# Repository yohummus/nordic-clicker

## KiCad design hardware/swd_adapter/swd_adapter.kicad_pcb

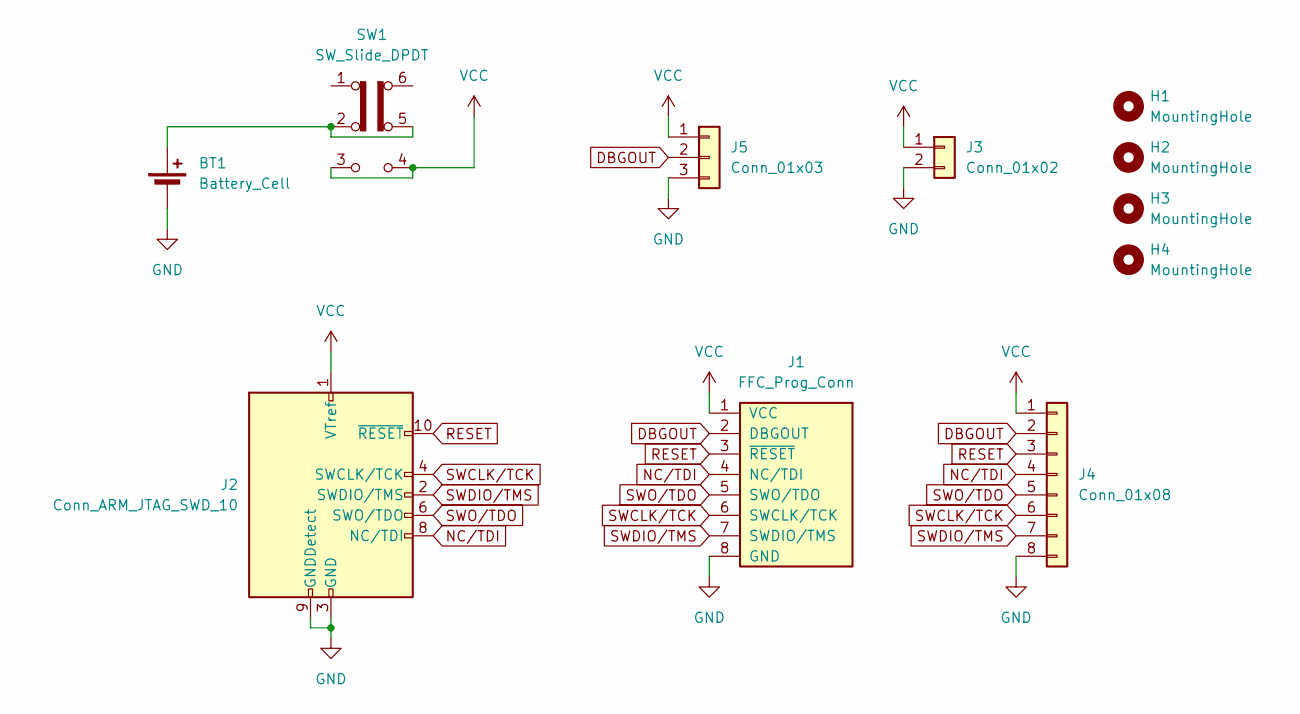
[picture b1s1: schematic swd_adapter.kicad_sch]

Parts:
BT1: Battery_Cell; BatteryHolder_Keystone_1060_1x2032; MPN 1060TR; Mouser-PN 534-1060TR
H1, H2, H3, H4: MountingHole; MountingHole_3.2mm_M3
J1: FFC_Prog_Conn; Molex_505110-0892; MPN 505110-0892; Mouser-PN 538-505110-0892
J2: Conn_ARM_JTAG_SWD_10; PinHeader_2x05_P1.27mm_Vertical_SMD; MPN 4048; Mouser-PN 485-4048
J3: Conn_01x02; PinHeader_1x02_P2.54mm_Vertical
J4: Conn_01x08; PinHeader_1x08_P2.54mm_Vertical
J5: Conn_01x03; PinHeader_1x03_P2.54mm_Vertical
SW1: SW_Slide_DPDT; SW_CK_JS202011CQN_DPDT_Straight; MPN JS202011CQN; Mouser-PN 611-JS202011CQN

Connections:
DBGOUT: J1.2 (DBGOUT), J4.2, J5.2
GND: BT1.2 (-), J1.8 (GND), J2.3 (GND), J2.5 (GND), J2.9 (GNDDetect), J3.2, J4.8, J5.3
NC/TDI: J1.4 (NC/TDI), J2.8 (NC/TDI), J4.4
unnamed: BT1.1 (+), SW1.2 (B), SW1.5 (B)
RESET: J1.3 (~RESET), J2.10 (~RESET), J4.3
SWCLK/TCK: J1.6 (SWCLK/TCK), J2.4 (SWCLK/TCK), J4.6
SWDIO/TMS: J1.7 (SWDIO/TMS), J2.2 (SWDIO/TMS), J4.7
SWO/TDO: J1.5 (SWO/TDO), J2.6 (SWO/TDO), J4.5
VCC: J1.1 (VCC), J2.1 (VTref), J3.1, J4.1, J5.1, SW1.3 (C), SW1.4 (A)

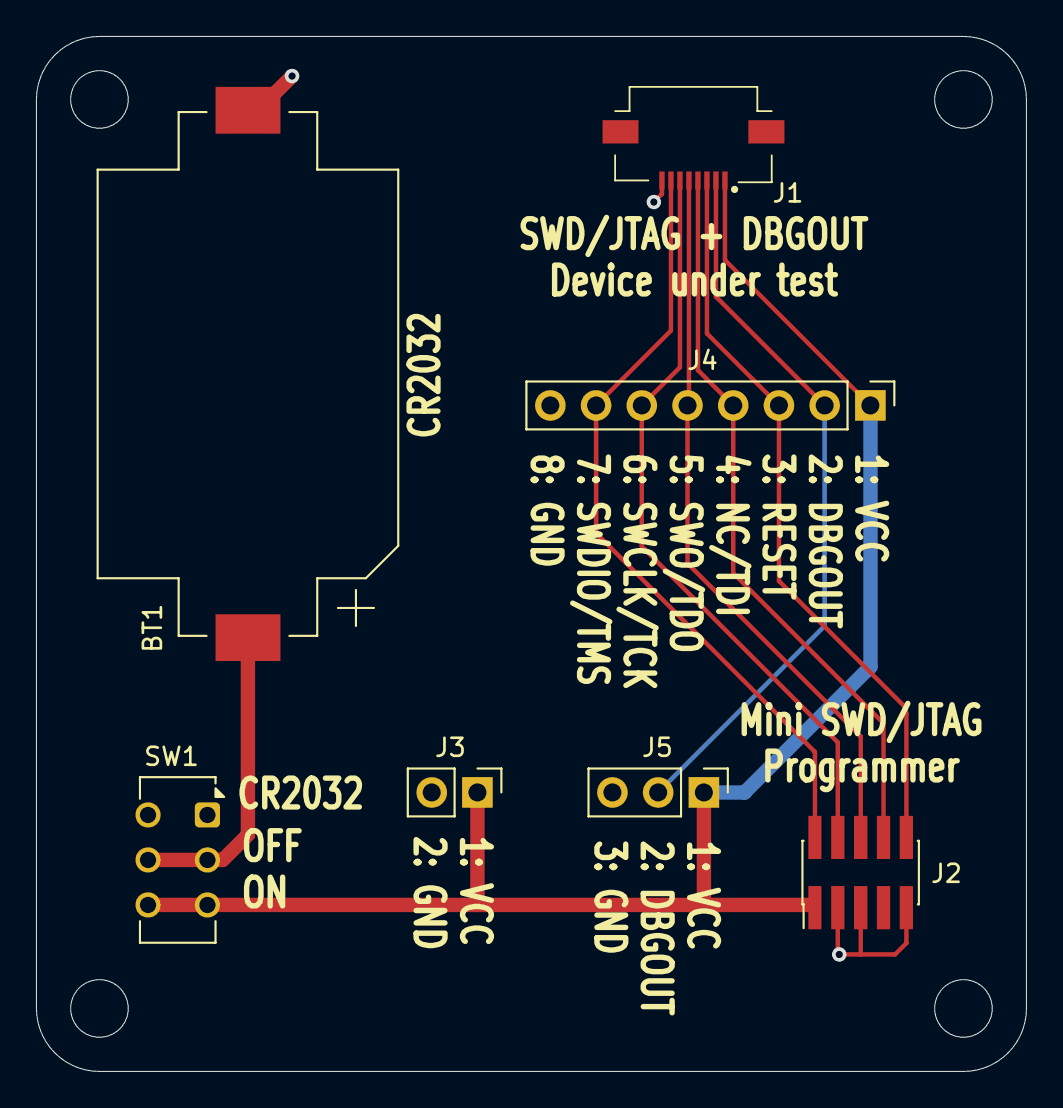
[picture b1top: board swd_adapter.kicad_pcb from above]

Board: 2 copper layers, 55.0 x 57.5 mm, 11 parts (0 on the bottom side), 9 nets.

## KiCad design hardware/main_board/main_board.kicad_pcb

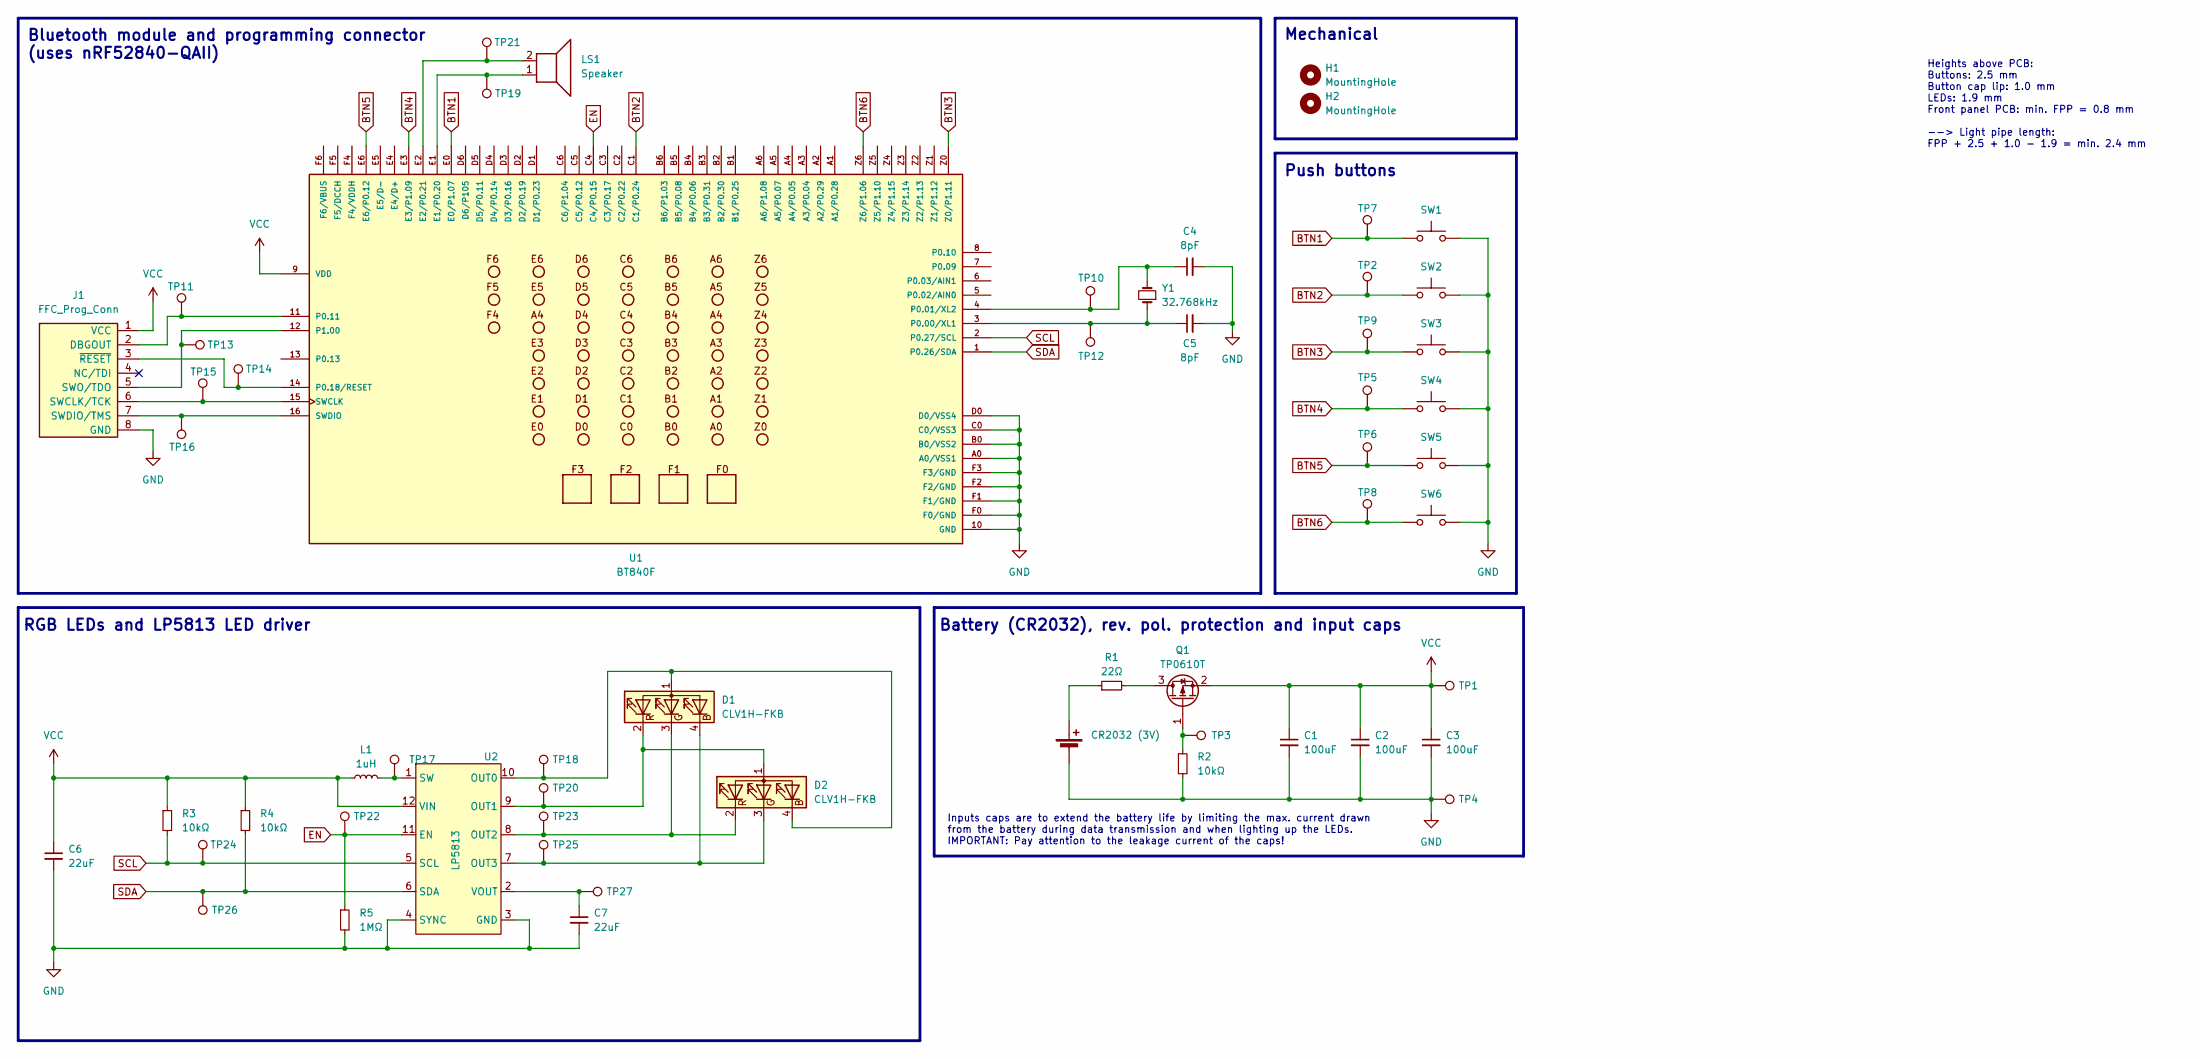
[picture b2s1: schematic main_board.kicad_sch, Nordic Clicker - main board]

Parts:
BT1: Keystone_2991; MPN 2991; Mouser-PN 534-2991
BT2: CR2032 (3V); BAT-HLD-001; MPN BAT-HLD-001; Mouser-PN 712-BAT-HLD-001
C1, C2, C3: 100uF; C_1206_3216Metric; Voltage 10V; Tolerance 20%; MPN C3216X5R1A107M160AC; Mouser-PN 810-C3216X5R1A107M
C4, C5: 8pF; C_0603_1608Metric; Voltage 25V; Tolerance 0.5pF; MPN 06033A8R0DAT2A; Mouser-PN 581-06033A8R0DAT2A
C6, C7: 22uF; C_0603_1608Metric; Voltage 16V; Tolerance 20%; MPN GRM188C61C226ME01J; Mouser-PN 81-GRM188C61C226ME1J
D1, D2: CLV1H-FKB; PLCC4_CLV1H-FKB; MPN CLV1H-FKB-CMPRTHKBB2367453; Mouser-PN 941-CLV1HBCTKB237453
H1, H2: MountingHole; Hole_2.5mm_Keepout_4mm
J1: FFC_Prog_Conn; Molex_505110-0892; MPN 505110-0892; Mouser-PN 538-505110-0892
L1: 1uH; SRP4020TA; MPN SRP4020TA-1R0M; Mouser-PN 652-SRP4020TA-1R0M
LS1: Speaker; Buzzer_Mallory_AST1109MLTRQ; MPN AST1109MLTRQ; Mouser-PN 539-AST1109MLTRQ
Q1: TP0610T; SOT-23; MPN SI2323DDS-T1-GE3; Mouser-PN 78-SI2323DDS-T1-GE3
R1: 22Ω; R_0603_1608Metric; Voltage 75V; Tolerance 1%; MPN CRCW060322R0FKEAC; Mouser-PN 71-CRCW060322R0FKEAC
R2, R3, R4: 10kΩ; R_0603_1608Metric; Voltage 75V; Tolerance 1%; MPN CRCW060310K0FKEAC; Mouser-PN 71-CRCW060310K0FKEAC
R5: 1MΩ; R_0603_1608Metric; Voltage 75V; Tolerance 1%; MPN CRCW06031M00FKEAC; Mouser-PN 71-CRCW06031M00FKEAC
SW1, SW2, SW3, SW4, SW5, SW6: PTS810SJG250SMTR LFS; PTS810; MPN PTS810SJG250SMTR LFS; Mouser-PN 611-PTS810SJG250SMTR
TP1, TP2, TP3, TP4, TP5, TP6, TP7, TP8, TP9, TP10, TP11, TP12, TP13, TP14, TP15, TP16, TP17, TP18, TP19, TP20, TP21, TP22, TP23, TP24, TP25, TP26, TP27: Test_Point; TestPoint_Pad_D1.0mm
U1: BT840F; MPN BT840F; Mouser-PN 308-BT840F
U2: LP5813; WSON-12; MPN LP5813CDRRR; Mouser-PN 595-LP5813CDRRR
Y1: 32.768kHz; ABS07AIG; MPN ABS07-32.768KHZ-9-T; Mouser-PN 815-ABS07-32.768K9T

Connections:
BTN1: SW1.2, TP7.1, U1.E0 (E0/P1.07)
BTN2: SW2.2, TP2.1, U1.C1 (C1/P0.24)
BTN3: SW3.2, TP9.1, U1.Z0 (Z0/P1.11)
BTN4: SW4.2, TP5.1, U1.E3 (E3/P1.09)
BTN5: SW5.2, TP6.1, U1.E6 (E6/P0.12)
BTN6: SW6.2, TP8.1, U1.Z6 (Z6/P1.06)
EN: R5.1, TP22.1, U1.C4 (C4/P0.15), U2.11 (EN)
GND: BT1.1 (-), C1.2, C2.2, C3.2, C4.2, C5.2, C6.2, C7.2, J1.8 (GND), R2.2, R5.2, SW1.1, SW2.1, SW3.1, SW4.1, SW5.1, SW6.1, TP4.1, U1.10 (GND), U1.A0 (A0/VSS1), U1.B0 (B0/VSS2), U1.C0 (C0/VSS3), U1.D0 (D0/VSS4), U1.F0 (F0/GND), U1.F1 (F1/GND), U1.F2 (F2/GND), U1.F3 (F3/GND), U2.3 (GND), U2.4 (SYNC), U2.13 (GND)
unnamed: BT2.1 (+), R1.1
unnamed: D1.1 (A), D2.4 (BK), TP18.1, U2.10 (OUT0)
unnamed: D1.4 (BK), D2.3 (GK), TP25.1, U2.7 (OUT3)
unnamed: D1.3 (GK), D2.2 (RK), TP23.1, U2.8 (OUT2)
unnamed: D1.2 (RK), D2.1 (A), TP20.1, U2.9 (OUT1)
unnamed: J1.2 (DBGOUT), TP11.1, U1.11 (P0.11)
unnamed: J1.6 (SWCLK/TCK), TP15.1, U1.15 (SWCLK)
unnamed: J1.7 (SWDIO/TMS), TP16.1, U1.16 (SWDIO)
unnamed: J1.5 (SWO/TDO), TP13.1, U1.12 (P1.00)
unnamed: J1.3 (~RESET), TP14.1, U1.14 (P0.18/RESET)
unnamed: Q1.3 (D), R1.2
unnamed: Q1.1 (G), R2.1, TP3.1
unnamed: LS1.1, TP19.1, U1.E1 (E1/P0.20)
unnamed: LS1.2, TP21.1, U1.E2 (E2/P0.21)
unnamed: C5.1, TP12.1, U1.3 (P0.00/XL1), Y1.1
unnamed: C4.1, TP10.1, U1.4 (P0.01/XL2), Y1.2
unnamed: L1.2, TP17.1, U2.1 (SW)
unnamed: C7.1, TP27.1, U2.2 (VOUT)
SCL: R3.2, TP24.1, U1.2 (P0.27/SCL), U2.5 (SCL)
SDA: R4.2, TP26.1, U1.1 (P0.26/SDA), U2.6 (SDA)
VCC: C1.1, C2.1, C3.1, C6.1, J1.1 (VCC), L1.1, Q1.2 (S), R3.1, R4.1, TP1.1, U1.9 (VDD), U2.12 (VIN)

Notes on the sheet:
Heights above PCB: Buttons: 2.5 mm Button cap lip: 1.0 mm LEDs: 1.9 mm Front panel PCB: min. FPP = 0.8 mm --> Light pipe length: FPP + 2.5 + 1.0 - 1.9 = min. 2.4 mm
Push buttons
Bluetooth module and programming connector (uses nRF52840-QAII)
Inputs caps are to extend the battery life by limiting the max. current drawn from the battery during data transmission and when lighting up the LEDs. IMPORTANT: Pay attention to the leakage current of the caps!
RGB LEDs and LP5813 LED driver
Battery (CR2032), rev. pol. protection and input caps
Mechanical

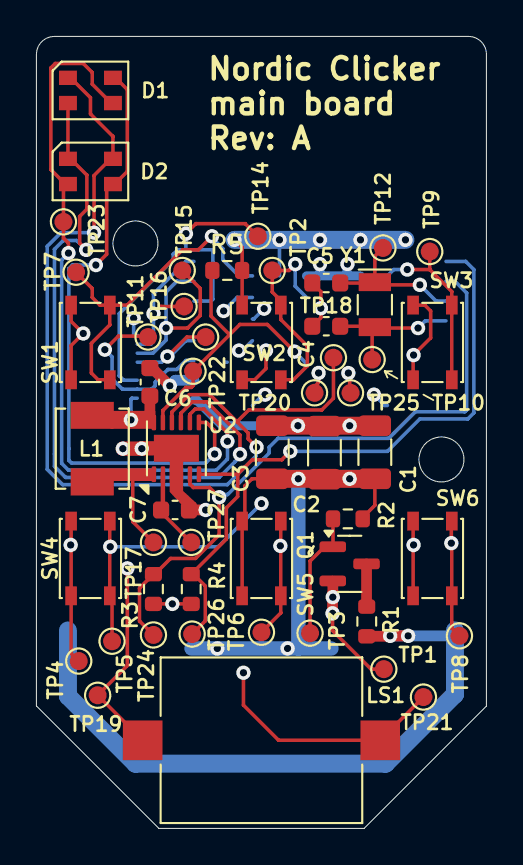
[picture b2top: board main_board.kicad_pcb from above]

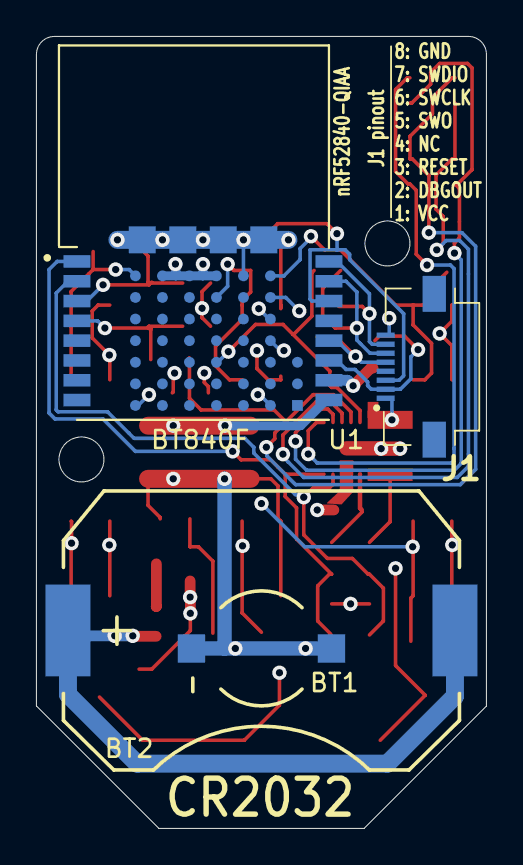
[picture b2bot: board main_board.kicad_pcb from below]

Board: 4 copper layers, 25.0 x 44.0 mm, 58 parts (4 on the bottom side), 29 nets.

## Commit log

2025-02-09 First draft of main board and front panel
2025-02-15 Rev. A finished
2025-02-15 Added firmware board and app skeletons
2025-02-16 Fleshed out Zephyr board and first small hardware test
2025-02-26 Updated KiCad files to version 9.0
2025-03-05 Got LEDs and DBGOUT working, however, logging to UART does not work
2025-03-22 Changed LEDs module to use FIFO and got UART for logging working
2025-03-24 Now playing Super Mario on the buzzer
2025-03-27 Got LED driver animations working
2025-03-29 Got button interrupts working
2025-03-31 Refactored buttons module to use thread
2025-04-01 Got button press detection after wakeup from sys off working
2025-04-01 Got first battery voltage measurement working
2025-04-03 Battery module implemented
2025-04-13 Added example receiver app template
2025-04-17 Got Gazell config changes working via Bluetooth
